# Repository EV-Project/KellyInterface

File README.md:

# KellyInterface
A hardware interface to link the Kelly motor controller to a CAN bus control scheme
This uses a digital Potentiometer to drive the throttle and brake signals, and BJTs to drive the microswitch inputs.

Includes a CAN and RS232 interface between the Kelly motor controller and a teensy3.2.
Also features a configurable E-stop line and hardware shutdown signal, RC charge-pump Watchdog timer, and access to the motor's hall effect outputs.

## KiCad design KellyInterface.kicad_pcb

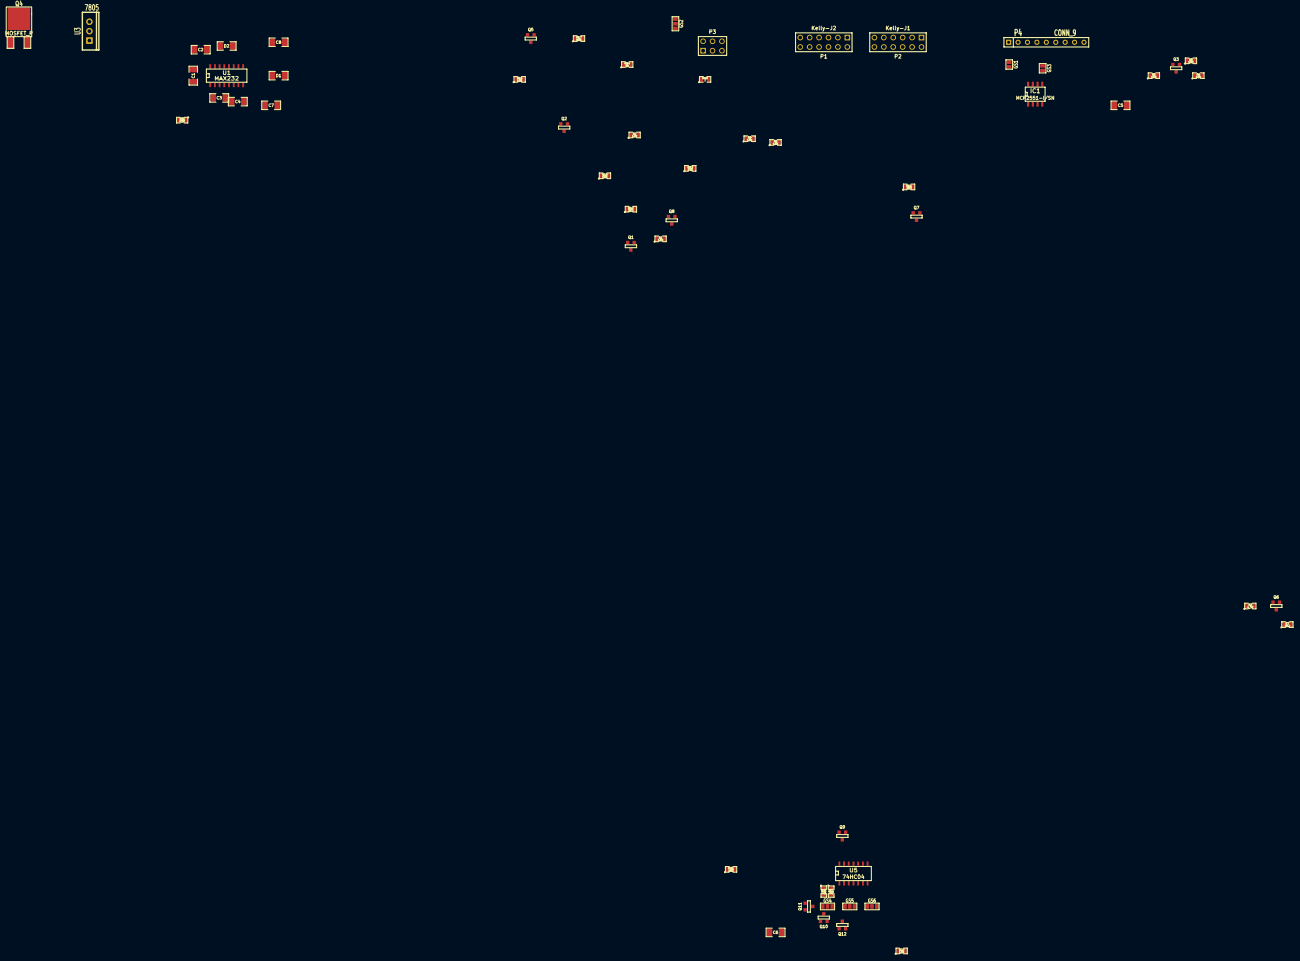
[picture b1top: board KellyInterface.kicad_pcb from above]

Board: 2 copper layers, 58 parts (0 on the bottom side), 52 nets, no tracks yet.

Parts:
C1, C2, C3, C4, C8: 1uF; SM1206
C5, C6, C7: 10uF; SM1206
D1, D2: DIODE; SM1206
GS1: CAN_H; GS2
GS2: GS3
GS3: CAN_L; GS2
GS4: WD_select; GS3
GS5: POT_select; GS3
GS6: INH_select; GS3
IC1: MCP2551-I/SN; SO8E
P1: Kelly-J2; pin_array_6x2
P2: Kelly-J1; pin_array_6x2
P3: Motor_Sig; pin_array_3x2
P4: CONN_9; SIL-9
Q1, Q2, Q3, Q5, Q6, Q7, Q8, Q10, Q11, Q12: NPN; SOT23EBC
Q4: MOSFET_P; DPAK2
Q9: PNP; SOT23EBC
R1, R2, R4, R5, R6, R8, R9, R10, R13, R15, R17, R18, R19, R20, R21, R22: 10K; SM0805
R3: 4.7K; SM0805
R7, R11, R12: 2K2; SM0805
R14: 1K; SM0805
R16: -; SM0805
U1: MAX232; SO16E
U3: 7805; TO220_VERT
U5: 74HC04; SO14E

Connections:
+5V: GS2.1, IC1.3, R20.2, U1.16
+24V: C5.1, P4.1, R6.1
/CAN_H: GS1.2, IC1.7, P4.3
/CAN_L: GS3.2, IC1.6, P4.4
/Kelly_5V_out: GS2.3, P1.7, Q9.1
/Kelly_Brake_switch: P1.10, Q7.3
/Kelly_CAN_H: GS1.1, P2.10
/Kelly_CAN_L: GS3.1, P2.11
/Kelly_Green_LED: P2.6, R2.1
/Kelly_Hall_A: P1.11, P3.5, R10.1
/Kelly_Hall_B: P1.12, P3.3, R9.1
/Kelly_Hall_C: P3.1, R8.1
/Kelly_Motor_temp: P1.4, Q9.3, R14.1
/Kelly_RS232_RX: P2.8, U1.14
/Kelly_RS232_TX: P2.9, U1.13
/Kelly_Reverse_switch: P1.9, Q8.3
/Kelly_Throttle_switch: P1.8, Q6.3
/Stops/ESTOP_Pin: GS6.3, U5.5, U5.8
/Stops/ESTOP_RAIL: GS4.3, P4.8, Q12.3, R19.2
/Stops/Motor_Disable: GS6.2, R17.1
/Stops/SHDN_Pin: GS6.1, U5.1, U5.4
/Stops/SHDN_RAIL: GS4.1, P4.7, Q11.3, R18.2
/Stops/WATCHDOG: GS4.2, Q10.3
/Stops/~ESTOP~_Pin: GS5.3, U5.6
/Stops/~SHDN~_Pin: GS5.1, U5.2
GND: C1.1, C2.1, C5.2, C6.2, C7.1, D2.2, IC1.2, P3.6, P4.2, Q1.1, Q2.1, Q3.1, Q5.1, Q6.1, Q7.1, Q8.1, Q10.1, Q11.1, Q12.1, R3.1, R14.2, U1.15, U5.7
unnamed: Q6.2, R7.1
unnamed: Q1.2, R1.1
unnamed: C4.2, U1.5
unnamed: C1.2, U1.2
unnamed: C2.2, U1.6
unnamed: Q2.2, R2.2
unnamed: C3.1, U1.1
unnamed: C3.2, U1.3
unnamed: C4.1, U1.4
unnamed: Q7.2, R11.2
unnamed: Q8.2, R12.1
unnamed: R5.1, R6.2
unnamed: Q3.3, R5.2
unnamed: GS2.2, P3.2, R16.1
unnamed: P3.4, R13.1, R16.2
unnamed: Q3.2, R4.2
unnamed: Q9.2, R15.1
unnamed: Q5.3, R15.2
unnamed: Q5.2, R17.2
unnamed: IC1.8, R3.2
unnamed: R19.1, U5.9
unnamed: Q11.2, R21.2
unnamed: Q12.2, R22.2
unnamed: R18.1, U5.3
unnamed: C8.1, D1.2, D2.1
unnamed: C7.2, D1.1, Q10.2, R20.1

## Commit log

2015-11-04 Basic Elements
2015-11-06 moved stops to new sheet
2015-11-07 Converted to Local and Hierarchical net labels
2015-11-10 added PDF export
2015-11-10 changed exports
